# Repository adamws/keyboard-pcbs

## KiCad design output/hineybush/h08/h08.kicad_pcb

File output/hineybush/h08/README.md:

## hineybush/h08

[layout](h08-kle.json) - [PCB](h08.kicad_pcb)

{:loading="lazy"}

[Open in keyboard-layout-editor](http://www.keyboard-layout-editor.com/##@@=0,0&=0,1&=0,2&=0,3;&@=1,0%0A%0A%0A0,0&=1,1%0A%0A%0A0,0&=1,2%0A%0A%0A1,0&=1,3%0A%0A%0A1,0;&@_y:0.25&w:2;&=1,0%0A%0A%0A0,1&_w:2;&=1,2%0A%0A%0A1,1)

{:loading="lazy"}

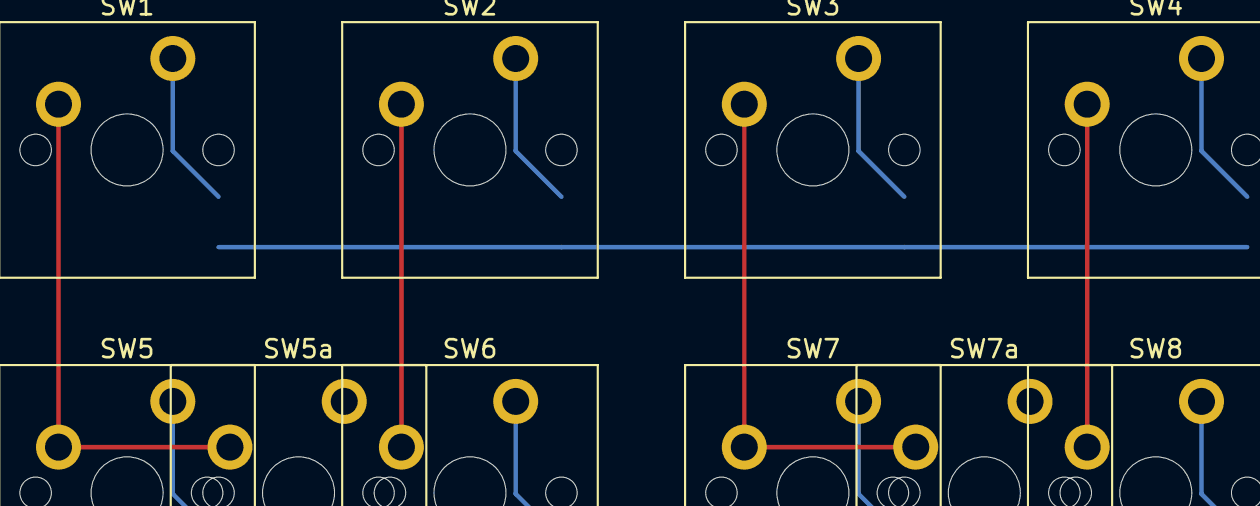
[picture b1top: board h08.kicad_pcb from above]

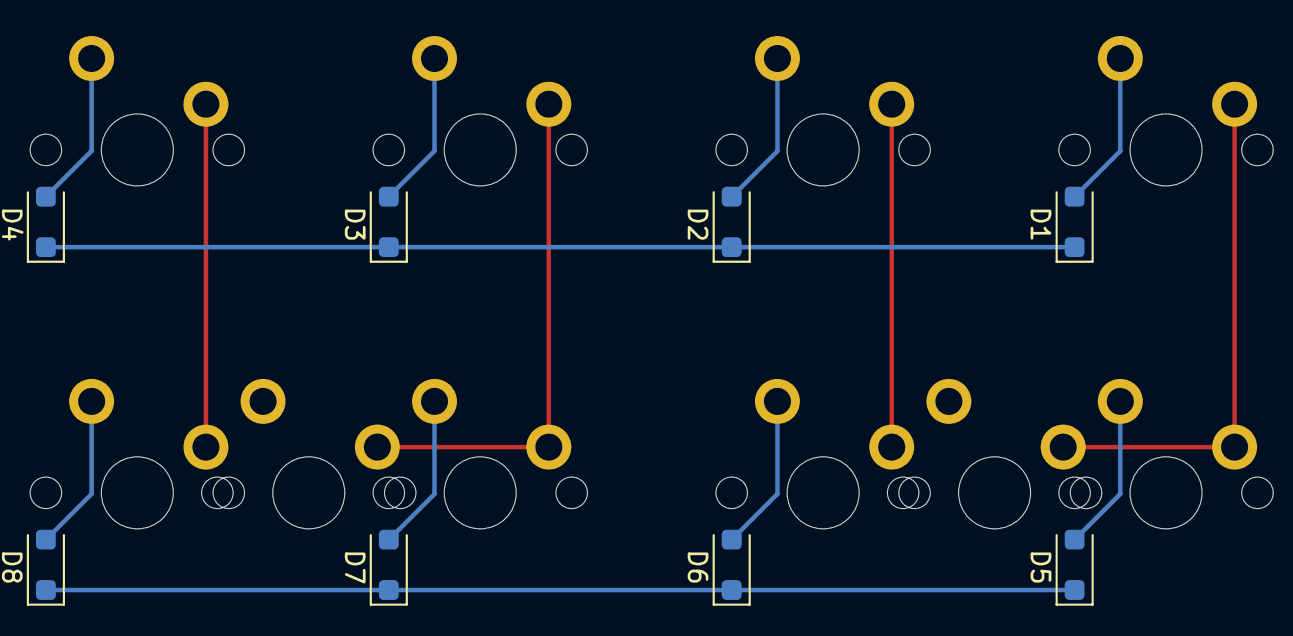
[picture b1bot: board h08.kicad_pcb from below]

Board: 2 copper layers, 18 parts (8 on the bottom side), 14 nets.

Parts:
D1, D2, D3, D4, D5, D6, D7, D8: D_SOD-123F
SW1, SW2, SW3, SW4, SW5, SW5a, SW6, SW7, SW7a, SW8: SW_Cherry_MX_PCB_1.00u

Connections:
COL0: SW1.1, SW5.1, SW5a.1
COL1: SW2.1, SW6.1
COL2: SW3.1, SW7.1, SW7a.1
COL3: SW4.1, SW8.1
unnamed: D1.2, SW1.2
unnamed: D2.2, SW2.2
unnamed: D3.2, SW3.2
unnamed: D4.2, SW4.2
unnamed: D5.2, SW5.2, SW5a.2
unnamed: D6.2, SW6.2
unnamed: D7.2, SW7.2, SW7a.2
unnamed: D8.2, SW8.2
ROW0: D1.1, D2.1, D3.1, D4.1
ROW1: D5.1, D6.1, D7.1, D8.1

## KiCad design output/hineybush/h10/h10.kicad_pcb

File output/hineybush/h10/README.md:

## hineybush/h10

[layout](h10-kle.json) - [PCB](h10.kicad_pcb)

{:loading="lazy"}

[Open in keyboard-layout-editor](http://www.keyboard-layout-editor.com/##@@_c=#aaaaaa;&=0,0&=0,1&=0,2&=0,3;&@_y:0.25;&=1,0&=1,1&=1,2&=1,3;&@_c=#cccccc;&=2,0&=2,1&=2,2&_c=#aaaaaa&h:2;&=3,3%0A%0A%0A0,0;&@_c=#cccccc;&=3,0&=3,1&=3,2;&@=4,0&=4,1&=4,2&_c=#777777&h:2;&=5,3%0A%0A%0A1,0;&@_c=#cccccc&w:2;&=5,1%0A%0A%0A2,0&=5,2;&@_x:4.25&y:-4.0&c=#aaaaaa;&=2,3%0A%0A%0A0,1;&@_x:4.25;&=3,3%0A%0A%0A0,1;&@_x:4.25;&=4,3%0A%0A%0A1,1;&@_x:4.25;&=5,3%0A%0A%0A1,1;&@_y:0.25&c=#cccccc;&=5,0%0A%0A%0A2,1&=5,1%0A%0A%0A2,1)

{:loading="lazy"}

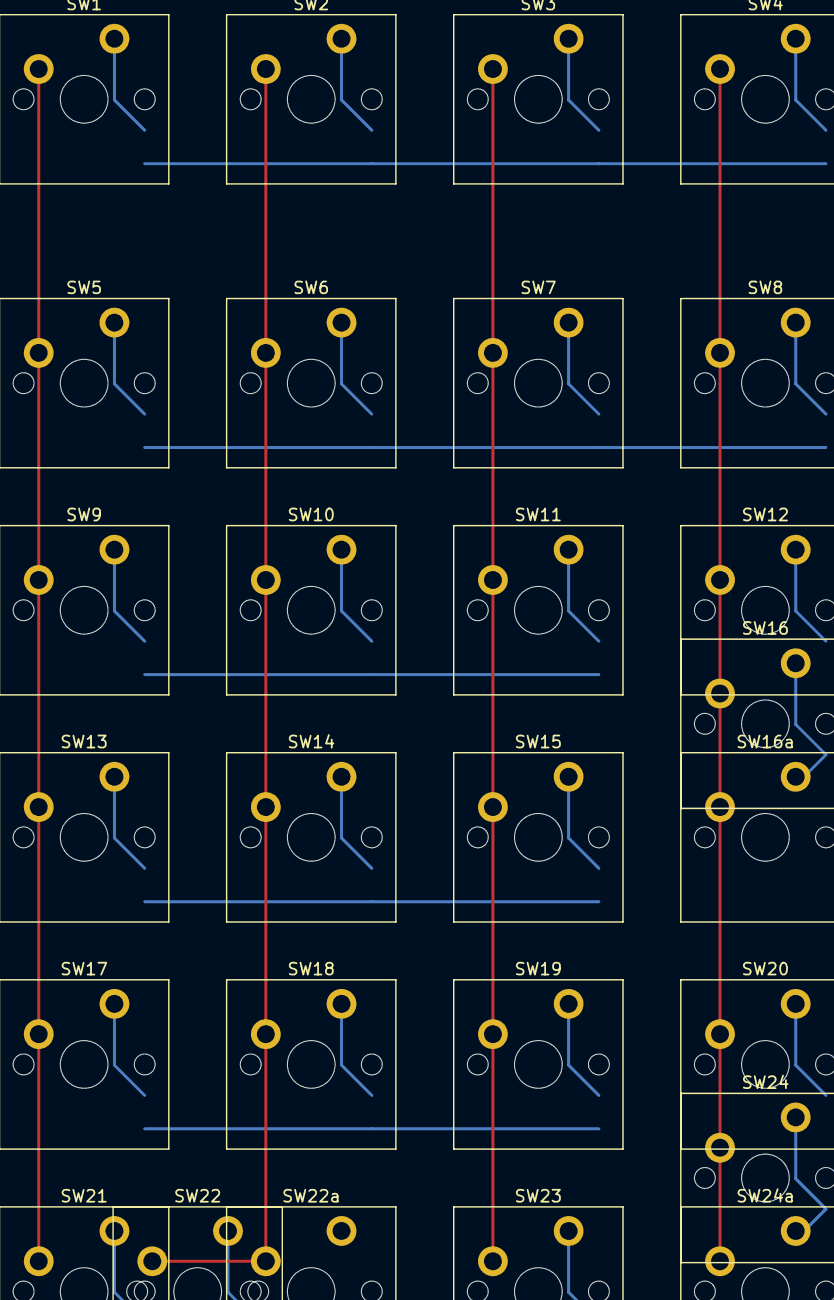
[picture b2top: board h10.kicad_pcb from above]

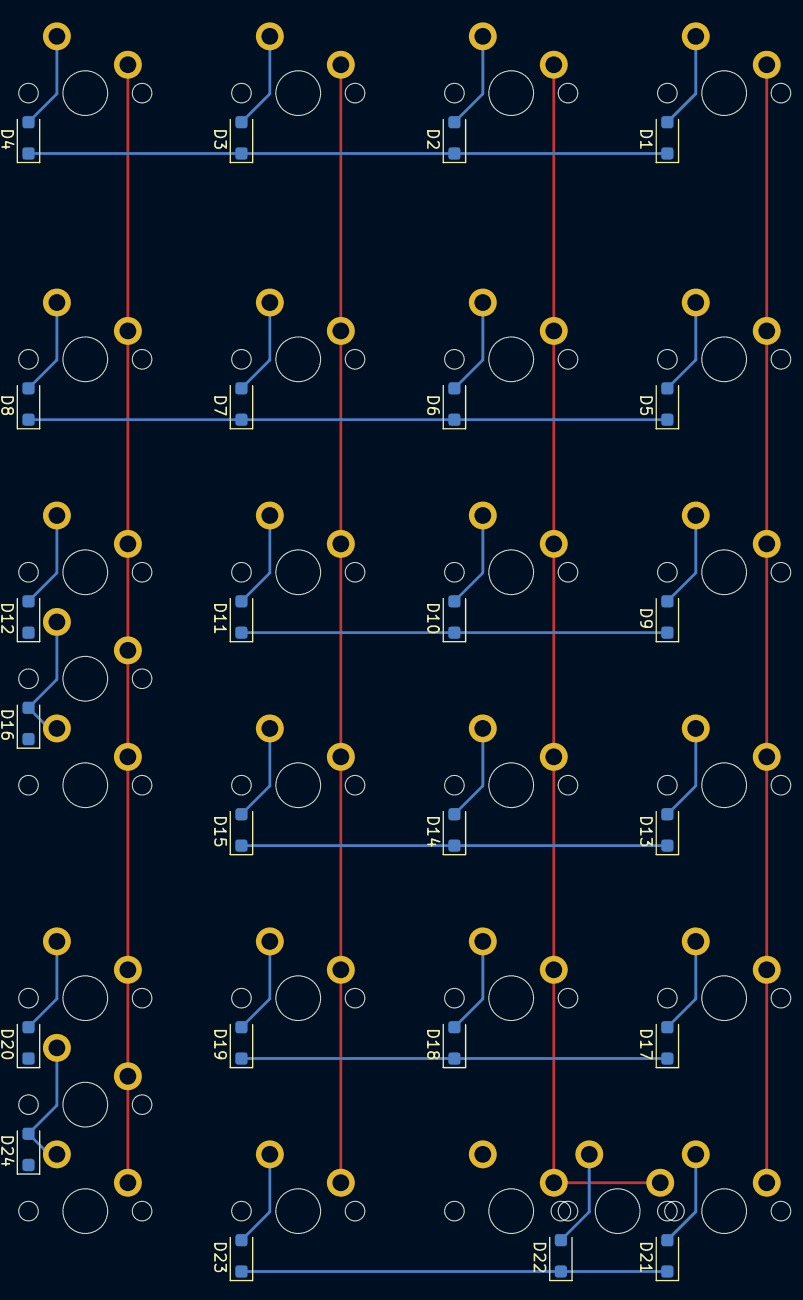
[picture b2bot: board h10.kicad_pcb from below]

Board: 2 copper layers, 51 parts (24 on the bottom side), 34 nets.

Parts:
D1, D2, D3, D4, D5, D6, D7, D8, D9, D10, D11, D12, D13, D14, D15, D16, D17, D18, D19, D20, D21, D22, D23, D24: D_SOD-123F
SW1, SW2, SW3, SW4, SW5, SW6, SW7, SW8, SW9, SW10, SW11, SW12, SW13, SW14, SW15, SW16, SW16a, SW17, SW18, SW19, SW20, SW21, SW22, SW22a, SW23, SW24, SW24a: SW_Cherry_MX_PCB_1.00u

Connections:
COL0: SW1.1, SW5.1, SW9.1, SW13.1, SW17.1, SW21.1
COL1: SW2.1, SW6.1, SW10.1, SW14.1, SW18.1, SW22.1, SW22a.1
COL2: SW3.1, SW7.1, SW11.1, SW15.1, SW19.1, SW23.1
COL3: SW4.1, SW8.1, SW12.1, SW16.1, SW16a.1, SW20.1, SW24.1, SW24a.1
unnamed: D1.2, SW1.2
unnamed: D2.2, SW2.2
unnamed: D3.2, SW3.2
unnamed: D4.2, SW4.2
unnamed: D5.2, SW5.2
unnamed: D6.2, SW6.2
unnamed: D7.2, SW7.2
unnamed: D8.2, SW8.2
unnamed: D9.2, SW9.2
unnamed: D10.2, SW10.2
unnamed: D11.2, SW11.2
unnamed: D12.2, SW12.2
unnamed: D13.2, SW13.2
unnamed: D14.2, SW14.2
unnamed: D15.2, SW15.2
unnamed: D16.2, SW16.2, SW16a.2
unnamed: D17.2, SW17.2
unnamed: D18.2, SW18.2
unnamed: D19.2, SW19.2
unnamed: D20.2, SW20.2
unnamed: D21.2, SW21.2
unnamed: D22.2, SW22.2, SW22a.2
unnamed: D23.2, SW23.2
unnamed: D24.2, SW24.2, SW24a.2
ROW0: D1.1, D2.1, D3.1, D4.1
ROW1: D5.1, D6.1, D7.1, D8.1
ROW2: D9.1, D10.1, D11.1, D12.1
ROW3: D13.1, D14.1, D15.1, D16.1
ROW4: D17.1, D18.1, D19.1, D20.1
ROW5: D21.1, D22.1, D23.1, D24.1

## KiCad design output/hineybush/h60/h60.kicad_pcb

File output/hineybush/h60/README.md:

## hineybush/h60

[layout](h60-kle.json) - [PCB](h60.kicad_pcb)

{:loading="lazy"}

[Open in keyboard-layout-editor](http://www.keyboard-layout-editor.com/##@@_x:5.5&c=#777777;&=0,0&_c=#cccccc;&=0,1&=0,2&=0,3&=0,4&=0,5&=0,6&=0,7&=0,8&=0,9&=0,10&=0,11&=0,12&_c=#aaaaaa&w:2;&=1,13%0A%0A%0A0,0;&@_x:5.5&c=#cccccc&w:1.5;&=1,0&=1,1&=1,2&=1,3&=1,4&=1,5&=1,6&=1,7&=1,8&=1,9&=1,10&=1,11&=1,12&_w:1.5;&=2,13%0A%0A%0A3,0;&@_x:5.5&c=#aaaaaa&w:1.75;&=2,0&_c=#cccccc;&=2,1&=2,2&=2,3&=2,4&=2,5&=2,6&=2,7&=2,8&=2,9&=2,10&=2,11&_c=#777777&w:2.25;&=2,12%0A%0A%0A3,0;&@_x:5.5&c=#aaaaaa&w:2.25;&=3,0%0A%0A%0A1,0&_c=#cccccc;&=3,1&=3,2&=3,3&=3,4&=3,5&=3,6&=3,7&=3,8&=3,9&=3,10&_c=#aaaaaa&w:2.75;&=3,11%0A%0A%0A2,0;&@_x:5.5&w:1.25;&=4,0%0A%0A%0A4,0&_w:1.25;&=4,1%0A%0A%0A4,0&_w:1.25;&=4,2%0A%0A%0A4,0&_c=#cccccc&w:6.25;&=4,6%0A%0A%0A4,0&_c=#aaaaaa&w:1.25;&=4,9%0A%0A%0A4,0&_w:1.25;&=4,10%0A%0A%0A4,0&_w:1.25;&=4,11%0A%0A%0A4,0&_w:1.25;&=4,12%0A%0A%0A4,0;&@_x:21.5&y:-5;&=0,13%0A%0A%0A0,1&=1,13%0A%0A%0A0,1;&@_x:22.5&c=#cccccc&w:1.25&h:2&w2:1.5&h2:1&x2:-0.25;&=2,12%0A%0A%0A3,1;&@_x:21.5&c=#aaaaaa;&=4,13%0A%0A%0A3,1;&@_x:2.25&w:1.25;&=3,0%0A%0A%0A1,1&=3,13%0A%0A%0A1,1&_x:17.0&w:1.75;&=3,11%0A%0A%0A2,1&=3,12%0A%0A%0A2,1;&@_x:5.5&y:1.25&c=#cccccc&w:1.5&d:true;&=4,0%0A%0A%0A4,1&_c=#aaaaaa;&=4,1%0A%0A%0A4,1&_w:1.5;&=4,2%0A%0A%0A4,1&_c=#cccccc&w:7;&=4,6%0A%0A%0A4,1&_c=#aaaaaa&w:1.5;&=4,10%0A%0A%0A4,1&=4,11%0A%0A%0A4,1&_c=#cccccc&w:1.5&d:true;&=4,12%0A%0A%0A4,1;&@_x:5.5&y:0.25&c=#aaaaaa&w:1.5;&=4,0%0A%0A%0A4,2&=4,1%0A%0A%0A4,2&_w:1.5;&=4,2%0A%0A%0A4,2&_c=#cccccc&w:7;&=4,6%0A%0A%0A4,2&_c=#aaaaaa&w:1.5;&=4,10%0A%0A%0A4,2&=4,11%0A%0A%0A4,2&_w:1.5;&=4,12%0A%0A%0A4,2;&@_x:5.5&y:0.25&w:1.5;&=4,0%0A%0A%0A4,3&_d:true;&=4,1%0A%0A%0A4,3&_w:1.5;&=4,2%0A%0A%0A4,3&_c=#cccccc&w:7;&=4,6%0A%0A%0A4,3&_c=#aaaaaa&w:1.5;&=4,10%0A%0A%0A4,3&_c=#cccccc&d:true;&=4,11%0A%0A%0A4,3&_c=#aaaaaa&w:1.5;&=4,12%0A%0A%0A4,3;&@_x:5.5&y:0.25&w:1.5;&=4,0%0A%0A%0A4,4&=4,1%0A%0A%0A4,4&_w:1.5;&=4,2%0A%0A%0A4,4&_c=#cccccc&w:2.75;&=4,3%0A%0A%0A4,4&_w:1.5;&=4,6%0A%0A%0A4,4&_w:2.75;&=4,8%0A%0A%0A4,4&_c=#aaaaaa&w:1.5;&=4,10%0A%0A%0A4,4&=4,11%0A%0A%0A4,4&_w:1.5;&=4,12%0A%0A%0A4,4)

{:loading="lazy"}

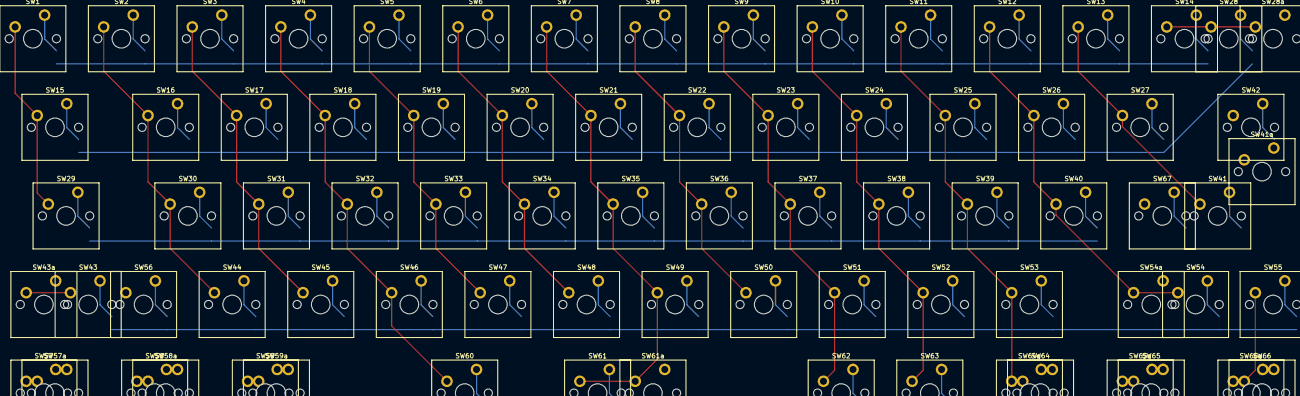
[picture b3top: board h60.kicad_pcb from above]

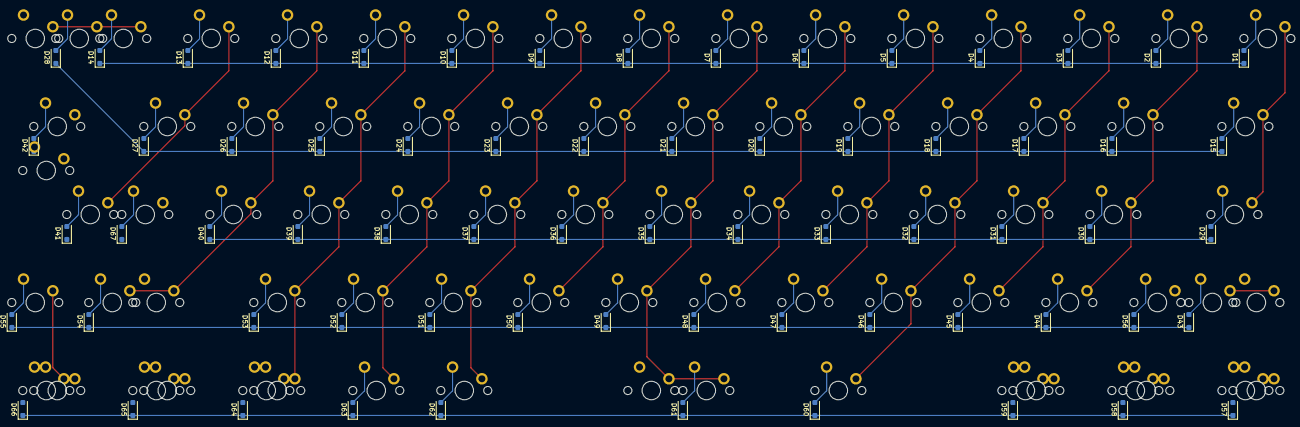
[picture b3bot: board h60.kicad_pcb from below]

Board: 2 copper layers, 145 parts (67 on the bottom side), 86 nets.

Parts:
D1, D2, D3, D4, D5, D6, D7, D8, D9, D10, D11, D12, D13, D14, D15, D16, D17, D18, D19, D20, D21, D22, D23, D24, D25, D26, D27, D28, D29, D30, D31, D32, D33, D34, D35, D36, D37, D38, D39, D40, D41, D42, D43, D44, D45, D46, D47, D48, D49, D50, D51, D52, D53, D54, D55, D56, D57, D58, D59, D60, D61, D62, D63, D64, D65, D66, D67: D_SOD-123F
SW1, SW2, SW3, SW4, SW5, SW6, SW7, SW8, SW9, SW10, SW11, SW12, SW13, SW14, SW15, SW16, SW17, SW18, SW19, SW20, SW21, SW22, SW23, SW24, SW25, SW26, SW27, SW28, SW28a, SW29, SW30, SW31, SW32, SW33, SW34, SW35, SW36, SW37, SW38, SW39, SW40, SW41, SW41a, SW42, SW43, SW43a, SW44, SW45, SW46, SW47, SW48, SW49, SW50, SW51, SW52, SW53, SW54, SW54a, SW55, SW56, SW57, SW57a, SW58, SW58a, SW59, SW59a, SW60, SW61, SW61a, SW62, SW63, SW64, SW64a, SW65, SW65a, SW66, SW66a, SW67: SW_Cherry_MX_PCB_1.00u

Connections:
COL0: SW1.1, SW15.1, SW29.1, SW43.1, SW43a.1, SW57.1, SW57a.1
COL1: SW2.1, SW16.1, SW30.1, SW44.1, SW58.1, SW58a.1
COL2: SW3.1, SW17.1, SW31.1, SW45.1, SW59.1, SW59a.1
COL3: SW4.1, SW18.1, SW32.1, SW46.1, SW60.1
COL4: SW5.1, SW19.1, SW33.1, SW47.1
COL5: SW6.1, SW20.1, SW34.1, SW48.1
COL6: SW7.1, SW21.1, SW35.1, SW49.1, SW61.1, SW61a.1
COL7: SW8.1, SW22.1, SW36.1, SW50.1
COL8: SW9.1, SW23.1, SW37.1, SW51.1, SW62.1
COL9: SW10.1, SW24.1, SW38.1, SW52.1, SW63.1
COL10: SW11.1, SW25.1, SW39.1, SW53.1, SW64.1, SW64a.1
COL11: SW12.1, SW26.1, SW40.1, SW54.1, SW54a.1, SW65.1, SW65a.1
COL12: SW13.1, SW27.1, SW41.1, SW41a.1, SW55.1, SW66.1, SW66a.1
COL13: SW14.1, SW28.1, SW28a.1, SW42.1, SW56.1, SW67.1
unnamed: D1.2, SW1.2
unnamed: D2.2, SW2.2
unnamed: D3.2, SW3.2
unnamed: D4.2, SW4.2
unnamed: D5.2, SW5.2
unnamed: D6.2, SW6.2
unnamed: D7.2, SW7.2
unnamed: D8.2, SW8.2
unnamed: D9.2, SW9.2
unnamed: D10.2, SW10.2
unnamed: D11.2, SW11.2
unnamed: D12.2, SW12.2
unnamed: D13.2, SW13.2
unnamed: D14.2, SW14.2
unnamed: D15.2, SW15.2
unnamed: D16.2, SW16.2
unnamed: D17.2, SW17.2
unnamed: D18.2, SW18.2
unnamed: D19.2, SW19.2
unnamed: D20.2, SW20.2
unnamed: D21.2, SW21.2
unnamed: D22.2, SW22.2
unnamed: D23.2, SW23.2
unnamed: D24.2, SW24.2
unnamed: D25.2, SW25.2
unnamed: D26.2, SW26.2
unnamed: D27.2, SW27.2
unnamed: D28.2, SW28.2, SW28a.2
unnamed: D29.2, SW29.2
unnamed: D30.2, SW30.2
unnamed: D31.2, SW31.2
unnamed: D32.2, SW32.2
unnamed: D33.2, SW33.2
unnamed: D34.2, SW34.2
unnamed: D35.2, SW35.2
unnamed: D36.2, SW36.2
unnamed: D37.2, SW37.2
unnamed: D38.2, SW38.2
unnamed: D39.2, SW39.2
unnamed: D40.2, SW40.2
unnamed: D41.2, SW41.2, SW41a.2
unnamed: D42.2, SW42.2
unnamed: D43.2, SW43.2, SW43a.2
unnamed: D44.2, SW44.2
unnamed: D45.2, SW45.2
unnamed: D46.2, SW46.2
unnamed: D47.2, SW47.2
unnamed: D48.2, SW48.2
unnamed: D49.2, SW49.2
unnamed: D50.2, SW50.2
unnamed: D51.2, SW51.2
unnamed: D52.2, SW52.2
unnamed: D53.2, SW53.2
unnamed: D54.2, SW54.2, SW54a.2
unnamed: D55.2, SW55.2
unnamed: D56.2, SW56.2
unnamed: D57.2, SW57.2, SW57a.2
unnamed: D58.2, SW58.2, SW58a.2
unnamed: D59.2, SW59.2, SW59a.2
unnamed: D60.2, SW60.2
unnamed: D61.2, SW61.2, SW61a.2
unnamed: D62.2, SW62.2
unnamed: D63.2, SW63.2
unnamed: D64.2, SW64.2, SW64a.2
unnamed: D65.2, SW65.2, SW65a.2
unnamed: D66.2, SW66.2, SW66a.2
unnamed: D67.2, SW67.2
ROW0: D1.1, D2.1, D3.1, D4.1, D5.1, D6.1, D7.1, D8.1, D9.1, D10.1, D11.1, D12.1, D13.1, D14.1
ROW1: D15.1, D16.1, D17.1, D18.1, D19.1, D20.1, D21.1, D22.1, D23.1, D24.1, D25.1, D26.1, D27.1, D28.1
ROW2: D29.1, D30.1, D31.1, D32.1, D33.1, D34.1, D35.1, D36.1, D37.1, D38.1, D39.1, D40.1, D41.1, D42.1
ROW3: D43.1, D44.1, D45.1, D46.1, D47.1, D48.1, D49.1, D50.1, D51.1, D52.1, D53.1, D54.1, D55.1, D56.1
ROW4: D57.1, D58.1, D59.1, D60.1, D61.1, D62.1, D63.1, D64.1, D65.1, D66.1, D67.1
